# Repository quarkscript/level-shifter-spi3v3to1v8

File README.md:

# Level shifter for plugging 1V8 spi flash chip to 3V3 flasher
Based on TXS0108E module.
Prototype was tested with CH341A flasher and W25Q32DWSIG spi flash.
https://youtu.be/cEi9tDHYepg

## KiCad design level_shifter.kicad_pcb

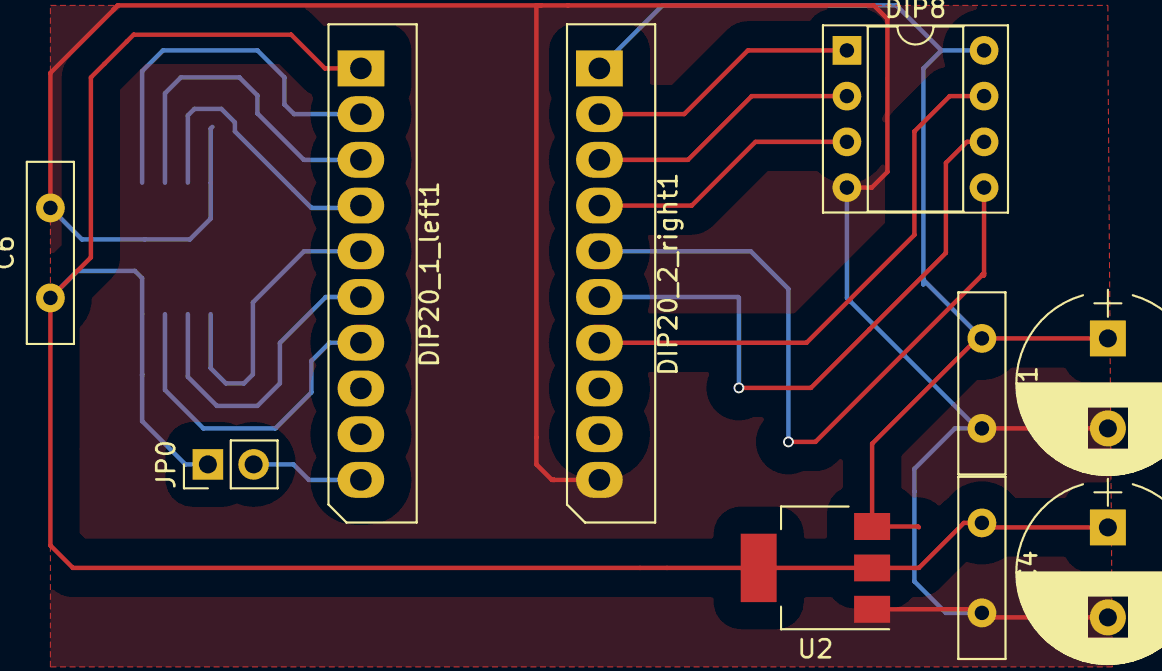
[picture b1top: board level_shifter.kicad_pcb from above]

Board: 2 copper layers, 11 parts (1 on the bottom side), 16 nets.

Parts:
C1, C4, C6: 104; C_Disc_D10.0mm_W2.5mm_P5.00mm
C2, C3: 10uF; CP_Radial_D10.0mm_P5.00mm
DIP8: connector_to_programmer; DIP-8_W7.62mm_Socket
DIP20_1_left1: connector_to_TXS0108E_1V8; Molex_SPOX-5267_22-03-5105_10x2.54mm_Straight
DIP20_2_right1: connector_to_TXS0108E_3V3; Molex_SPOX-5267_22-03-5105_10x2.54mm_Straight
JP0: nc; Pin_Header_Straight_1x02_Pitch2.54mm
U1: 25LC_EEPROM; SOIJ-8_5.3x5.3mm_Pitch1.27mm
U2: LD1117S18TR_SOT223; SOT-223-3_TabPin2

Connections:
unnamed: DIP20_1_left1.2, U1.1
unnamed: DIP20_1_left1.3, U1.2
unnamed: DIP20_1_left1.4, U1.3
unnamed: C1.2, C2.2, C3.2, C4.2, C6.2, DIP8.4, DIP20_2_right1.10, U1.4, U2.1
unnamed: DIP20_1_left1.5, U1.5
unnamed: DIP20_1_left1.6, U1.6
unnamed: DIP20_1_left1.7, U1.7
unnamed: C3.1, C4.1, C6.1, DIP20_1_left1.1, JP0.1, U1.8, U2.2
unnamed: C1.1, C2.1, DIP8.8, DIP20_2_right1.1, U2.3
unnamed: DIP20_1_left1.10, JP0.2
unnamed: DIP8.1, DIP20_2_right1.2
unnamed: DIP8.2, DIP20_2_right1.3
unnamed: DIP8.3, DIP20_2_right1.4
unnamed: DIP8.5, DIP20_2_right1.5
unnamed: DIP8.6, DIP20_2_right1.6
unnamed: DIP8.7, DIP20_2_right1.7
